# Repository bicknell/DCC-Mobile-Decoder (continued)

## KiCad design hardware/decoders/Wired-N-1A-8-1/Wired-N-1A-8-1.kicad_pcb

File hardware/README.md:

# Hardware

* [conventions](conventions/) contains documentation of hardware conventions
  used across all designs in this project.
* [reference](reference/) designs are used to understand DCC and develop
  software.  They are generally not suitable to put in a locomotive.
* [decoders](decoders/) are mobile decoders suitable for putting into 
  locomotives designed to work with the same general software as the 
  reference decoders.
* [kicad_libraries](kicad_libraries/) contains a symbol and footprint
  library that contains symbols used by the project that do not come
  with the stock KiCad distribution.

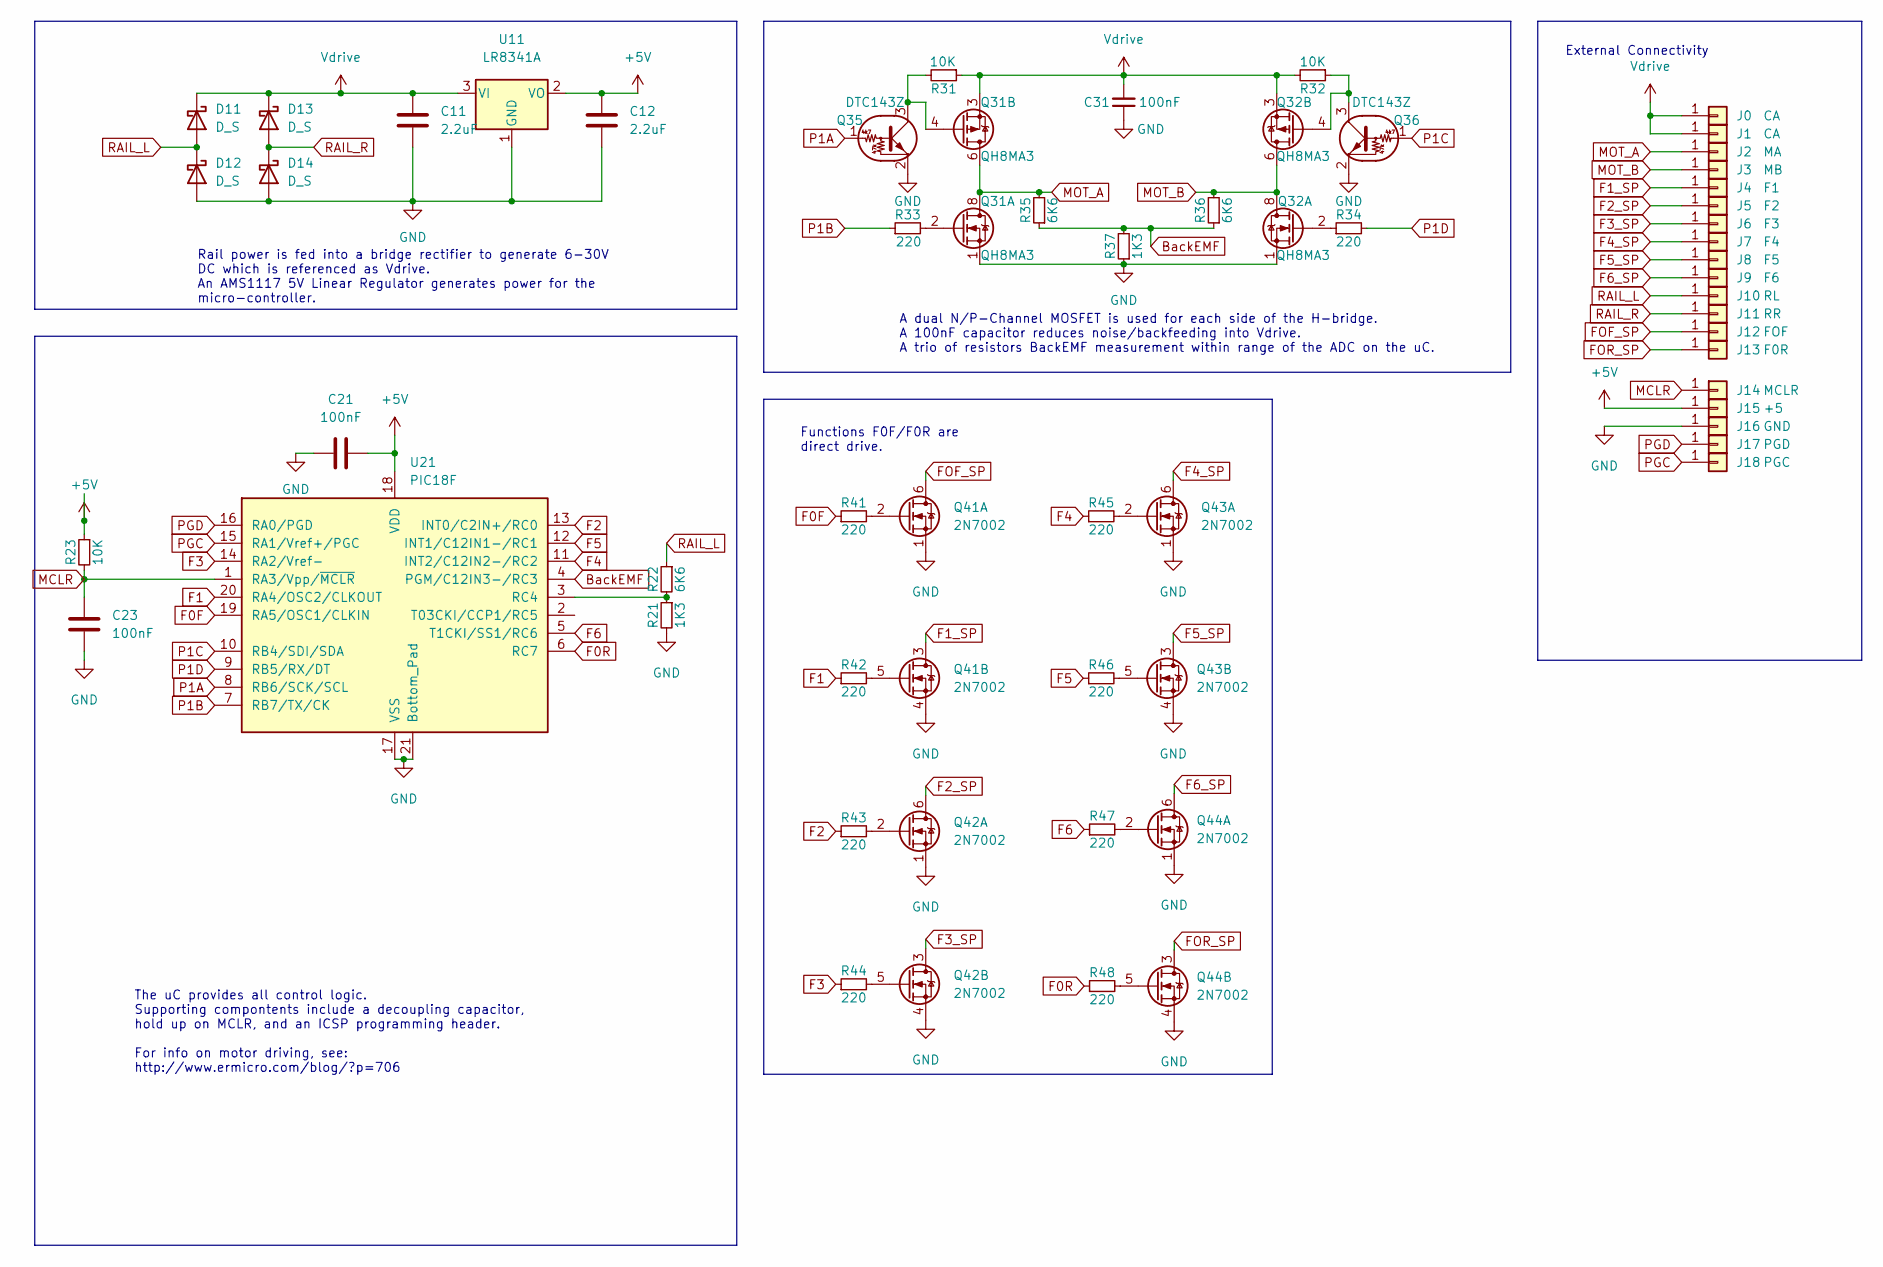
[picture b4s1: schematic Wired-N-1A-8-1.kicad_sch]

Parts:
C11, C12: 2.2uF; C_0402_1005Metric; MPN1 GRM155R6YA225KE11D
C21, C23: 100nF; C_0201_0603Metric; MPN1 GRM033R61E104KE14D
C31: 100nF; C_0402_1005Metric; MPN1 GRM155R61H104KE14D
D11, D12, D13, D14: D_S; D_SOD-523; MPN1 MSK4010
J0, J1: CA; SolderWirePad_1x01_SMD_1x2mm; MPN1 DNP
J2: MA; SolderWirePad_1x01_SMD_1x2mm; MPN1 DNP
J3: MB; SolderWirePad_1x01_SMD_1x2mm; MPN1 DNP
J4: F1; SolderWirePad_1x01_SMD_1x2mm; MPN1 DNP
J5: F2; SolderWirePad_1x01_SMD_1x2mm; MPN1 DNP
J6: F3; SolderWirePad_1x01_SMD_1x2mm; MPN1 DNP
J7: F4; SolderWirePad_1x01_SMD_1x2mm; MPN1 DNP
J8: F5; SolderWirePad_1x01_SMD_1x2mm; MPN1 DNP
J9: F6; SolderWirePad_1x01_SMD_1x2mm; MPN1 DNP
J10: RL; SolderWirePad_1x01_SMD_1x2mm; MPN1 DNP
J11: RR; SolderWirePad_1x01_SMD_1x2mm; MPN1 DNP
J12: FOF; SolderWirePad_1x01_SMD_1x2mm; MPN1 DNP
J13: F0R; SolderWirePad_1x01_SMD_1x2mm; MPN1 DNP
J14: MCLR; SolderWirePad_1x01_SMD_1x2mm; MPN1 DNP
J15: +5; SolderWirePad_1x01_SMD_1x2mm; MPN1 DNP
J16: GND; SolderWirePad_1x01_SMD_1x2mm; MPN1 DNP
J17: PGD; SolderWirePad_1x01_SMD_1x2mm; MPN1 DNP
J18: PGC; SolderWirePad_1x01_SMD_1x2mm; MPN1 DNP
Q31, Q32: QH8MA3; TSMT8; MPN1 QH8MA3 QH8MA3
Q35, Q36: DTC143Z; SOT-723; MPN1 DTC143ZM
Q41, Q42, Q43, Q44: 2N7002; SOT-363_SC-70-6; MPN1 2N7002KD
R21, R37: 1K3; R_0201_0603Metric; MPN1 0201WMF1331TEE
R22, R35, R36: 6K6; R_0201_0603Metric; MPN1 0201WMF665KTEE
R23: 10K; R_0201_0603Metric; MPN1 0201WMF1002TEE
R31, R32: 10K; R_0201_0603Metric; MPN1 0201WMF2200TEE
R33, R34, R41, R42, R43, R44, R45, R46, R47, R48: 220; R_0201_0603Metric; MPN1 0201WMF2200TEE
U11: LR8341A; SOT-23; MPN1 LR8341A-T50
U21: PIC18F; VQFN-20-1EP_3x3mm_P0.4mm_EP1.7x1.7mm; MPN1 PIC18F06Q40

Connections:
+5V: C12.1, C21.2, J15.1, R23.1, U11.2 (VO), U21.18 (VDD)
BackEMF: R35.1, R36.1, R37.2, U21.4 (PGM/C12IN3-/RC3)
F0F: R41.1, U21.19 (RA5/OSC1/CLKIN)
F0R: R48.1, U21.6 (RC7)
F1: R42.1, U21.20 (RA4/OSC2/CLKOUT)
F1_SP: J4.1, Q41.3 (D)
F2: R43.1, U21.13 (INT0/C2IN+/RC0)
F2_SP: J5.1, Q42.6 (D)
F3: R44.1, U21.14 (RA2/Vref-)
F3_SP: J6.1, Q42.3 (D)
F4: R45.1, U21.11 (INT2/C12IN2-/RC2)
F4_SP: J7.1, Q43.6 (D)
F5: R46.1, U21.12 (INT1/C12IN1-/RC1)
F5_SP: J8.1, Q43.3 (D)
F6: R47.1, U21.5 (T1CKI/SS1/RC6)
F6_SP: J9.1, Q44.6 (D)
FOF_SP: J12.1, Q41.6 (D)
FOR_SP: J13.1, Q44.3 (D)
GND: C11.2, C12.2, C21.1, C23.1, C31.1, D12.2 (A), D14.2 (A), J16.1, Q31.1 (S), Q32.1 (S), Q35.2 (E), Q36.2 (E), Q41.1 (S), Q41.4 (S), Q42.1 (S), Q42.4 (S), Q43.1 (S), Q43.4 (S), Q44.1 (S), Q44.4 (S), R21.2, R37.1, U11.1 (GND), U21.17 (VSS), U21.21 (Bottom_Pad)
MCLR: C23.2, J14.1, R23.2, U21.1 (RA3/Vpp/~MCLR)
MOT_A: J2.1, Q31.5 (D), Q31.6 (D), Q31.7 (D), Q31.8 (D), R35.2
MOT_B: J3.1, Q32.5 (D), Q32.6 (D), Q32.7 (D), Q32.8 (D), R36.2
unnamed: Q31.2 (G), R33.2
unnamed: Q32.2 (G), R34.1
unnamed: Q31.4 (G), Q35.3 (C), R31.2
unnamed: Q41.2 (G), R41.2
unnamed: Q41.5 (G), R42.2
unnamed: Q42.2 (G), R43.2
unnamed: Q42.5 (G), R44.2
unnamed: Q43.2 (G), R45.2
unnamed: Q43.5 (G), R46.2
unnamed: Q44.2 (G), R47.2
unnamed: Q44.5 (G), R48.2
unnamed: R21.1, R22.2, U21.3 (RC4)
unnamed: Q32.4 (G), Q36.3 (C), R32.1
P1A: Q35.1 (B), U21.8 (RB6/SCK/SCL)
P1B: R33.1, U21.7 (RB7/TX/CK)
P1C: Q36.1 (B), U21.10 (RB4/SDI/SDA)
P1D: R34.2, U21.9 (RB5/RX/DT)
PGC: J18.1, U21.15 (RA1/Vref+/PGC)
PGD: J17.1, U21.16 (RA0/PGD)
RAIL_L: D11.2 (A), D12.1 (K), J10.1, R22.1
RAIL_R: D13.2 (A), D14.1 (K), J11.1
Vdrive: C11.1, C31.2, D11.1 (K), D13.1 (K), J0.1, J1.1, Q31.3 (1), Q32.3 (1), R31.1, R32.2, U11.3 (VI)

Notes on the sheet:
External Connectivity
The uC provides all control logic. Supporting compontents include a decoupling capacitor, hold up on MCLR, and an ICSP programming header. For info on motor driving, see: http://www.ermicro.com/blog/?p=706
A dual N/P-Channel MOSFET is used for each side of the H-bridge. A 100nF capacitor reduces noise/backfeeding into Vdrive. A trio of resistors BackEMF measurement within range of the ADC on the uC.
Functions F0F/F0R are direct drive.
Rail power is fed into a bridge rectifier to generate 6-30V DC which is referenced as Vdrive. An AMS1117 5V Linear Regulator generates power for the micro-controller.

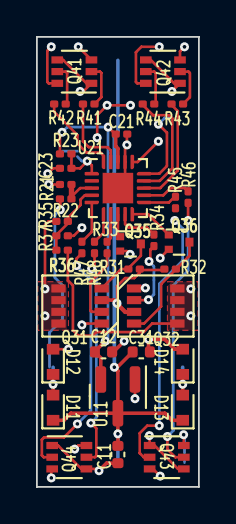
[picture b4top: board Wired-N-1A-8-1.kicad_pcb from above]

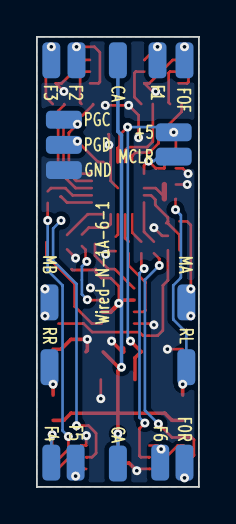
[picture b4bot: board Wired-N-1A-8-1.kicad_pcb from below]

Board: 2 copper layers, 9.0 x 25.0 mm, 56 parts (19 on the bottom side), 44 nets.

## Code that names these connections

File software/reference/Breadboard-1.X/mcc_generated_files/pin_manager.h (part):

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// get/set IO_F1 aliases
#define IO_F1_TRIS                 TRISAbits.TRISA0
#define IO_F1_LAT                  LATAbits.LATA0
#define IO_F1_PORT                 PORTAbits.RA0
#define IO_F1_WPU                  WPUAbits.WPUA0
#define IO_F1_OD                   ODCONAbits.ODCA0
#define IO_F1_ANS                  ANSELAbits.ANSELA0
#define IO_F1_SetHigh()            do { LATAbits.LATA0 = 1; } while(0)
#define IO_F1_SetLow()             do { LATAbits.LATA0 = 0; } while(0)
#define IO_F1_Toggle()             do { LATAbits.LATA0 = ~LATAbits.LATA0; } while(0)
#define IO_F1_GetValue()           PORTAbits.RA0
#define IO_F1_SetDigitalInput()    do { TRISAbits.TRISA0 = 1; } while(0)
#define IO_F1_SetDigitalOutput()   do { TRISAbits.TRISA0 = 0; } while(0)
#define IO_F1_SetPullup()          do { WPUAbits.WPUA0 = 1; } while(0)
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// get/set IO_F2 aliases
#define IO_F2_TRIS                 TRISAbits.TRISA1
#define IO_F2_LAT                  LATAbits.LATA1
#define IO_F2_PORT                 PORTAbits.RA1
#define IO_F2_WPU                  WPUAbits.WPUA1
#define IO_F2_OD                   ODCONAbits.ODCA1
#define IO_F2_ANS                  ANSELAbits.ANSELA1
#define IO_F2_SetHigh()            do { LATAbits.LATA1 = 1; } while(0)
#define IO_F2_SetLow()             do { LATAbits.LATA1 = 0; } while(0)
#define IO_F2_Toggle()             do { LATAbits.LATA1 = ~LATAbits.LATA1; } while(0)
#define IO_F2_GetValue()           PORTAbits.RA1
#define IO_F2_SetDigitalInput()    do { TRISAbits.TRISA1 = 1; } while(0)
#define IO_F2_SetDigitalOutput()   do { TRISAbits.TRISA1 = 0; } while(0)
#define IO_F2_SetPullup()          do { WPUAbits.WPUA1 = 1; } while(0)
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// get/set IO_F3 aliases
#define IO_F3_TRIS                 TRISAbits.TRISA2
#define IO_F3_LAT                  LATAbits.LATA2
#define IO_F3_PORT                 PORTAbits.RA2
#define IO_F3_WPU                  WPUAbits.WPUA2
#define IO_F3_OD                   ODCONAbits.ODCA2
#define IO_F3_ANS                  ANSELAbits.ANSELA2
#define IO_F3_SetHigh()            do { LATAbits.LATA2 = 1; } while(0)
#define IO_F3_SetLow()             do { LATAbits.LATA2 = 0; } while(0)
#define IO_F3_Toggle()             do { LATAbits.LATA2 = ~LATAbits.LATA2; } while(0)
#define IO_F3_GetValue()           PORTAbits.RA2
#define IO_F3_SetDigitalInput()    do { TRISAbits.TRISA2 = 1; } while(0)
#define IO_F3_SetDigitalOutput()   do { TRISAbits.TRISA2 = 0; } while(0)
#define IO_F3_SetPullup()          do { WPUAbits.WPUA2 = 1; } while(0)
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// get/set IO_DCC aliases
#define IO_DCC_TRIS                 TRISAbits.TRISA4
#define IO_DCC_LAT                  LATAbits.LATA4
#define IO_DCC_PORT                 PORTAbits.RA4
#define IO_DCC_WPU                  WPUAbits.WPUA4
#define IO_DCC_OD                   ODCONAbits.ODCA4
#define IO_DCC_ANS                  ANSELAbits.ANSELA4
#define IO_DCC_SetHigh()            do { LATAbits.LATA4 = 1; } while(0)
#define IO_DCC_SetLow()             do { LATAbits.LATA4 = 0; } while(0)
#define IO_DCC_Toggle()             do { LATAbits.LATA4 = ~LATAbits.LATA4; } while(0)
#define IO_DCC_GetValue()           PORTAbits.RA4
#define IO_DCC_SetDigitalInput()    do { TRISAbits.TRISA4 = 1; } while(0)
#define IO_DCC_SetDigitalOutput()   do { TRISAbits.TRISA4 = 0; } while(0)
#define IO_DCC_SetPullup()          do { WPUAbits.WPUA4 = 1; } while(0)
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// get/set IO_BACKEMF aliases
#define IO_BACKEMF_TRIS                 TRISAbits.TRISA5
#define IO_BACKEMF_LAT                  LATAbits.LATA5
#define IO_BACKEMF_PORT                 PORTAbits.RA5
#define IO_BACKEMF_WPU                  WPUAbits.WPUA5
#define IO_BACKEMF_OD                   ODCONAbits.ODCA5
#define IO_BACKEMF_ANS                  ANSELAbits.ANSELA5
#define IO_BACKEMF_SetHigh()            do { LATAbits.LATA5 = 1; } while(0)
#define IO_BACKEMF_SetLow()             do { LATAbits.LATA5 = 0; } while(0)
#define IO_BACKEMF_Toggle()             do { LATAbits.LATA5 = ~LATAbits.LATA5; } while(0)
#define IO_BACKEMF_GetValue()           PORTAbits.RA5
#define IO_BACKEMF_SetDigitalInput()    do { TRISAbits.TRISA5 = 1; } while(0)
#define IO_BACKEMF_SetDigitalOutput()   do { TRISAbits.TRISA5 = 0; } while(0)
#define IO_BACKEMF_SetPullup()          do { WPUAbits.WPUA5 = 1; } while(0)
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// get/set IO_F0R aliases
#define IO_F0R_TRIS                 TRISBbits.TRISB4
#define IO_F0R_LAT                  LATBbits.LATB4
#define IO_F0R_PORT                 PORTBbits.RB4
#define IO_F0R_WPU                  WPUBbits.WPUB4
#define IO_F0R_OD                   ODCONBbits.ODCB4
#define IO_F0R_ANS                  ANSELBbits.ANSELB4
#define IO_F0R_SetHigh()            do { LATBbits.LATB4 = 1; } while(0)
#define IO_F0R_SetLow()             do { LATBbits.LATB4 = 0; } while(0)
#define IO_F0R_Toggle()             do { LATBbits.LATB4 = ~LATBbits.LATB4; } while(0)
#define IO_F0R_GetValue()           PORTBbits.RB4
#define IO_F0R_SetDigitalInput()    do { TRISBbits.TRISB4 = 1; } while(0)
#define IO_F0R_SetDigitalOutput()   do { TRISBbits.TRISB4 = 0; } while(0)
#define IO_F0R_SetPullup()          do { WPUBbits.WPUB4 = 1; } while(0)
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#define RB5_SetHigh()            do { LATBbits.LATB5 = 1; } while(0)
#define RB5_SetLow()             do { LATBbits.LATB5 = 0; } while(0)
#define RB5_Toggle()             do { LATBbits.LATB5 = ~LATBbits.LATB5; } while(0)
#define RB5_GetValue()              PORTBbits.RB5
#define RB5_SetDigitalInput()    do { TRISBbits.TRISB5 = 1; } while(0)
#define RB5_SetDigitalOutput()   do { TRISBbits.TRISB5 = 0; } while(0)
#define RB5_SetPullup()             do { WPUBbits.WPUB5 = 1; } while(0)
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// get/set IO_F0F aliases
#define IO_F0F_TRIS                 TRISBbits.TRISB6
#define IO_F0F_LAT                  LATBbits.LATB6
#define IO_F0F_PORT                 PORTBbits.RB6
#define IO_F0F_WPU                  WPUBbits.WPUB6
#define IO_F0F_OD                   ODCONBbits.ODCB6
#define IO_F0F_ANS                  ANSELBbits.ANSELB6
#define IO_F0F_SetHigh()            do { LATBbits.LATB6 = 1; } while(0)
#define IO_F0F_SetLow()             do { LATBbits.LATB6 = 0; } while(0)
#define IO_F0F_Toggle()             do { LATBbits.LATB6 = ~LATBbits.LATB6; } while(0)
#define IO_F0F_GetValue()           PORTBbits.RB6
#define IO_F0F_SetDigitalInput()    do { TRISBbits.TRISB6 = 1; } while(0)
#define IO_F0F_SetDigitalOutput()   do { TRISBbits.TRISB6 = 0; } while(0)
#define IO_F0F_SetPullup()          do { WPUBbits.WPUB6 = 1; } while(0)
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#define RB7_SetHigh()            do { LATBbits.LATB7 = 1; } while(0)
#define RB7_SetLow()             do { LATBbits.LATB7 = 0; } while(0)
#define RB7_Toggle()             do { LATBbits.LATB7 = ~LATBbits.LATB7; } while(0)
#define RB7_GetValue()              PORTBbits.RB7
#define RB7_SetDigitalInput()    do { TRISBbits.TRISB7 = 1; } while(0)
#define RB7_SetDigitalOutput()   do { TRISBbits.TRISB7 = 0; } while(0)
#define RB7_SetPullup()             do { WPUBbits.WPUB7 = 1; } while(0)
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// get/set IO_F4 aliases
#define IO_F4_TRIS                 TRISCbits.TRISC0
#define IO_F4_LAT                  LATCbits.LATC0
#define IO_F4_PORT                 PORTCbits.RC0
#define IO_F4_WPU                  WPUCbits.WPUC0
#define IO_F4_OD                   ODCONCbits.ODCC0
#define IO_F4_ANS                  ANSELCbits.ANSELC0
#define IO_F4_SetHigh()            do { LATCbits.LATC0 = 1; } while(0)
#define IO_F4_SetLow()             do { LATCbits.LATC0 = 0; } while(0)
#define IO_F4_Toggle()             do { LATCbits.LATC0 = ~LATCbits.LATC0; } while(0)
#define IO_F4_GetValue()           PORTCbits.RC0
#define IO_F4_SetDigitalInput()    do { TRISCbits.TRISC0 = 1; } while(0)
#define IO_F4_SetDigitalOutput()   do { TRISCbits.TRISC0 = 0; } while(0)
#define IO_F4_SetPullup()          do { WPUCbits.WPUC0 = 1; } while(0)
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// get/set IO_F5 aliases
#define IO_F5_TRIS                 TRISCbits.TRISC1
#define IO_F5_LAT                  LATCbits.LATC1
#define IO_F5_PORT                 PORTCbits.RC1
#define IO_F5_WPU                  WPUCbits.WPUC1
#define IO_F5_OD                   ODCONCbits.ODCC1
#define IO_F5_ANS                  ANSELCbits.ANSELC1
#define IO_F5_SetHigh()            do { LATCbits.LATC1 = 1; } while(0)
#define IO_F5_SetLow()             do { LATCbits.LATC1 = 0; } while(0)
#define IO_F5_Toggle()             do { LATCbits.LATC1 = ~LATCbits.LATC1; } while(0)
#define IO_F5_GetValue()           PORTCbits.RC1
#define IO_F5_SetDigitalInput()    do { TRISCbits.TRISC1 = 1; } while(0)
#define IO_F5_SetDigitalOutput()   do { TRISCbits.TRISC1 = 0; } while(0)
#define IO_F5_SetPullup()          do { WPUCbits.WPUC1 = 1; } while(0)
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// get/set IO_F6 aliases
#define IO_F6_TRIS                 TRISCbits.TRISC2
#define IO_F6_LAT                  LATCbits.LATC2
#define IO_F6_PORT                 PORTCbits.RC2
#define IO_F6_WPU                  WPUCbits.WPUC2
#define IO_F6_OD                   ODCONCbits.ODCC2
#define IO_F6_ANS                  ANSELCbits.ANSELC2
#define IO_F6_SetHigh()            do { LATCbits.LATC2 = 1; } while(0)
#define IO_F6_SetLow()             do { LATCbits.LATC2 = 0; } while(0)
#define IO_F6_Toggle()             do { LATCbits.LATC2 = ~LATCbits.LATC2; } while(0)
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
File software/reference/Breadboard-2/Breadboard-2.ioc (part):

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Mcu.Name=STM32F103R(8-B)Tx
Mcu.Package=LQFP64
Mcu.UserName=STM32F103RBTx
PA12.GPIOParameters=GPIO_PuPd,GPIO_Label
PA12.GPIO_Label=DCC_IN
PA12.GPIO_PuPd=GPIO_PULLUP
PA12.Signal=S_TIM1_ETR
PA13.Mode=Serial_Wire
PA13.Signal=SYS_JTMS-SWDIO
PA14.Mode=Serial_Wire
PA14.Signal=SYS_JTCK-SWCLK
PA2.Mode=Asynchronous
PA2.Signal=USART2_TX
PA3.Mode=Asynchronous
PA3.Signal=USART2_RX
PA5.GPIOParameters=GPIO_Speed,PinState,GPIO_Label
PA5.GPIO_Label=STATUS_LED
PA5.GPIO_Speed=GPIO_SPEED_FREQ_LOW
PA5.PinState=GPIO_PIN_RESET
PA5.Signal=GPIO_Output
RCC.SYSCLKFreq_VALUE=64000000
RCC.SYSCLKSource=RCC_SYSCLKSOURCE_PLLCLK
board=custom

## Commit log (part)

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2022-11-08 Adding LICENSE and basic directory structure.
2022-11-08 First draft of hardware constraints.
2022-11-08 More constraints for the initial list.
2022-11-11 Ignore KiCAD temporary files.
2022-11-11 Initial reference design PCB commit.
2022-11-11 Cleaned up the PCB routing.
2022-11-11 Initial description of the schematic and PCB.
2022-11-12 More basic info added.
2022-11-12 Added CALCULATIONS information.
2022-11-12 Change from +12v to Vdrive.
2022-11-12 Added Contributing section.
2022-11-13 Update data sheet values and calculations. Add missing components.
2022-11-13 Added data sheets. Moved schematic values for readability.
2022-11-13 Lots of cleanup, finalizing the specifications for Breadboard-1.
2022-11-13 Added resistor and capacitor data.
2022-11-13 Added MOSFET specifications.
2022-11-13 Minor corrections to the overview document. Refill PCB.
2022-11-24 Add a 3D render of the board.
2022-11-24 Crop better.
2022-11-24 Shrink size.
2022-11-24 Added V3V3USB capacitor and USB Micro-B port for debugging.
2022-11-24 Move USB to the External Connectivity section.
2022-11-24 Update notes to be more clear about circuit design.
2022-11-24 Regenerate image to match current schematic.
2022-11-24 Make functions symmetrical.
2022-12-01 Made Wired-N-1A-6-1 prettier, and easier to follow.
2022-12-01 Moved to SOD-123 diodes for cheaper, better rating parts.
2022-12-01 Add a blank project for the DCC library, created in MPLabX
2022-12-08 Chip selection update, new symbols, improved reference design.
    Updated the chip selection document based on availability.
    Added new symbols for the chips in the chip selection document.
    Switched the reference design to an SSOP-20 package and improved the
    layout in general.
2022-12-08 Initial draft of feature documentation.
2022-12-08 Update to github Markdown syntax.
2022-12-08 Making the documentation more clear and organized.
2022-12-08 Make links match directory names.
2022-12-08 Correct nesting of lists.
2022-12-08 Organize the index a bit better.
2022-12-08 Update to PIC18F06Q40 specifications.
2022-12-08 Minor doc updates to go with the updated CPU.
2022-12-08 Updated to the new processor and lots of board layout cleanup.
2022-12-12 Updating the current project status.
2022-12-12 Position cleanup, better trace routing.
2022-12-12 Fixed typo, updated about future.
2022-12-12 Image to match the latest board.
2022-12-12 Add a listing of other projects.
2022-12-12 Added 3D render.
2022-12-12 Fix image syntax.
2022-12-12 Updated commercial license description.
2022-12-12 Initial documentation of IDE config.
2022-12-13 Add a PDF version of the schematic.
2022-12-13 Fixed broadcast decoder reset packet handling.
    Ran "make clean" before comitting, which is removing all of the build
    artifacts.
    Regenerated MCC files.
2022-12-13 Implement suggestions from DCC-EX friends.
    Set TMR2 period to 80us.
    Implemented consist address feature.
    Move variables out of dcc_decode and into globals for performance.
    Moved checksum inside dcc_decode to make interface cleaner.
    Reordered logic to check the speed/direction packets first, and the
    function group packets second to improve performance.
2022-12-13 All debugs should be turned off in the master repo.
2022-12-13 Clean up CV29/NDOT handling.
2022-12-13 Properly implement C19 consisting, including function mapping by CV21/CV22.
    Clean up some bad printf's with extra arguments.
    Improve NDOT (and consisted NDOT) handling in motor_control.
2022-12-14 Populate software index.
2022-12-14 Initial documentation of the features and functionality supported by the code.
2022-12-14 Implement read-only CV's.
2022-12-14 Correct typo, flag read only CV's.
2022-12-16 Clarified the current state of the project.
2022-12-17 Initial version of a fully manual breadboard version of the circuit.
2022-12-17 Add a few more details.
2022-12-17 Initial version of Manual-1.
2022-12-17 Minor tweak to BOM.
2022-12-17 Added a picture with some explanation.
2022-12-19 Initial support for S-9.2.3 service mode programming.
    Address mode.
    Direct mode.
    Register mode.
    Paged mode.
    Does not yet support either appendix.
2022-12-19 Update status on service mode.
2022-12-19 Updated feature list with Service Mode information.
2022-12-20 Reset handling improvement, fixed bit logic, cleaned Page/Register code.
2022-12-22 Add pre-biased transistors to drive high side. Update LED part to more common.
2022-12-22 Updated schematic PDF based on last edits.
2022-12-22 Updated TMR0 to 20ms, implemented dropping from Service Mode.
    Renamed dcc_performance to dcc_periodic to better reflect it's function.
    Set TMR0 to call it every 20ms.
    Update statitics printing to continue to be once per second.
    Implement dropping out of a service mode.
    Move the CV8=8 factory reset logic into the CV handling so that
    it works no matter how the CV is written.
2022-12-23 Bring inline with SOT-23 rework.
2022-12-27 Extended the refactor to include a DRV8870DDA motor driver.
    Generates parts reduction, at a slightly increased cost.
2023-02-19 Initial take at function effects.
    Changes TMR0 periodic to 25ms to create 40 bits/sec of output.
    Adds CV's 120-126 for function effect selection.
    Adds function_control() in hardware.c to manipulate the output.
    Adds effects[][] array in hardware.c with the bitpatterns for the output.
    Note that several of these are incomplete at this time.
2023-09-08 Added pin-header for oscilloscope.
    Provide connection points to monitor the DCC signal, motor driver
    inputs and backEMF.
    Additional prettying up of the traces.
2023-09-08 Bring documentation inline with previous technical updates.
2023-09-10 Cleanup of the final PCB.
    Moved components to grid coordinates.
    Added in some labels for the user.
    Cleaned up some trace routing, and made it pretty where possible.
2023-09-10 Generated updated .JPG and .PDF for documentation.
2023-09-11 Minor design tweak, update documentation.
    Moved the MCLEAR hold up components to make the board design cleaner.
    Updated all the documentation to match the current configuration.
2023-09-11 Add warning about resistor to README.
2023-09-11 Bring inline with Breadboard-1 reference design.
    Add digital transitor drivers for the high side of the H-Bridge.
    Add third BEMF resistor.
    Relocate noise capacitor.
2023-09-14 Manufacturability changes.
    Added 3 fiducial markers to support pick and place in volume.
    Resized all the traces to be manufacturable with the popular board fabs.
    Moved traces based on the new size.
    Standardized vias to one size larger than the general manufacturing minimum.
    Improved grounding around the CPU.
2023-09-15 Updated BOM to optimize for JLCPCB production.
    Used as many JLCPCB "basic" parts as possible, optimized for
    the cheapest parts in stock as of today.
2023-09-15 Updates based on feedback from JLCPCB online tools.
2023-09-16 Ignore more OSX cache files.
2023-09-16 Pile of minor corrections for sharing and production.
    1. Remove .DS_Store files mistakenly added.
    2. Correctly relatively path project footprints and symbols.
    3. Add footprint for JLCPCB's required tooling hole to use their assembly service.
    4. Tweak a few tracks and description placements to enhance readability.
2023-09-16 Add service mode programming note.
2023-09-16 Turned feature list into checkboxes to track progress.
2023-09-16 Minor cleanup.
2023-09-16 Remove unused directory.
2023-09-18 Moved CALCULATIONS to a spreadsheet.
    Moved the calculations into a spreadsheet so that the values would
    dynamically change when components needed to be updated. Used the
    dynamic capabilities along with the JLCPCB parts list to update
    resistor values to have more common values and use JLCPCB basic
    parts values.
    Determined also that the calculations on the DCC input were wrong
2023-09-18 Added missing ground trace and regenerated image.
2023-09-18 Save JLCPCB preferred gerber options.
2023-09-18 Missed 'Load En' in previous rework.
2023-09-18 Update board color to blue w/white silkscreen.
2023-09-19 Initial draft of a super-mineature F0F/F0R N-scale decoder.
2023-09-20 Added pngs as required by subreddit rules.
2023-09-20 Updated png files to make things more clear.
2023-09-20 Update CHIP-SELECTION.md
    Correct error in N/Z chip form factor. REB part numbers are VFQN-20 parts.
2023-09-24 Renamed Wired-N-1A-6-1 to Wired-N-1A-8-1.
2023-09-25 Improved calculations, and other updates as a result.
    Switched to tantalum capacitors per the data sheet recommendation
    for the regulator. Reworked board to accomodate.
    Switched DCC input to be through a MOSFET to accomodate the track
    voltage range.
    Re-organized schematic so the blocks make more sense, changed to
    US Letter paper, and re-annotated so each block has it's own 10's
2023-09-25 Fixed broken links and generated image and schematics.
2023-09-26 Switched regulator, added "super capacitor" location.
    Switched the linear regulator to a SE8633X2-HF which has superior
    performance characteristics. Switched back to 0805 10uF resistors
    as a result. Reworked regulator area, using copper fills to lower
    resistance between components per data sheet recomendation.
    Added C11, a spot for an electrolytic "super capacitor" of up to 1000uF
    to help smooth out input electrical issues. Moved a few traces to make
2023-09-26 Crop picture to the right size.
2023-09-26 Updated description to include super capacitor.
2023-09-27 Minor corrections to specs.
2023-09-27 Crop image.
2023-09-29 Plot paramters to get good gerbers.
2023-10-02 Correct over-voltage on high side drive.
    The P-Channel MOSFET gate would be driven to 0v by the old driver
    circuit. When the DCC voltage is > 20v, this exceeds the Vgs
    maximum of the part.
    Added another resistor to make a voltage divider cutting the voltage
    in half, and thus driving the gate at 15v when Vdrive is 30v. Now
    Vgs is always within range of the part.
2023-10-02 Initial draft of the decoder.
2023-10-04 Clarified function numbering.
2023-10-04 Ensure power traces can handle 1A, cosmetic cleanup.
    1) Enlarged traces that will carry large currents to insure they
    are of sufficient size.
    2) Make sure everything was aligned on an inch/mil grid. Moved components
    to provide more board space for the wider traces. General make it pretty.
2023-10-04 Fixed up text on the fab layer.
2023-10-04 Small corrections.
2023-10-04 Update to be current.
2023-10-06 Software with working function effects & motor control.
    Implemented basic function effects, some look good, some still
    need tweaking.
    Corrected the motor control code so the outputs are correct.
2023-10-06 Correct lighting features.
2023-10-06 Had NDOT listed twice.
2023-10-06 Cosmetic cleanup, removed unnecessary global scoped variables.
2023-10-07 Updated MOSFETS to be ESD protected versions. Updated calculations.
2023-10-08 Parts update, moved descriptive language from README to CALCULATIONS.
    Updated MOSFET selection, again.
    Moved all block descriptions from README into CALCULATIONS so they are
    not duplicated.
    Improved some descriptions.
2023-10-18 Improve manufacturability.
2023-10-18 Updated image to match manufacturability improvements.
2023-10-22 Initial hardware implementation of a STM32 processor.
    Replace the SSOP-20 PIC18F processor with a TSSOP-20 STM32 processor.
    Where possible IO was kept on the same pin number to avoid re-routing
    additonal traces. Minor changes were needed to the decoupling capacitors
    as well as the programming header.
2023-10-22 Correct data sheet link.
2023-10-22 Replace +5V to +3V3 in schematic to properly reflect voltage.
2023-10-22 Move DCC_IN and BackEMF to pins with appropriate capabilities.
    STM32 does not allow software remapping of the periperhal input
    pins. The location in the PIC design (Breadboard-1) routes them
    to pins on an STM32 that are designed for the oscellator, but can
    be re-used. As such they have no ADC or Timer triggers attached
    to them.
    DCC_IN was moved to port 20, which can be routed to any of
2024-03-18 Initial partial port of software to the STM32 platform.
    This code is destined to go with Breadboard-2, but for now is being
    developed and tested on an NUCLEO-F103RB board. It's done in
    STM32CubeIDE and uses the full set of hardware abstrations.
    The motor code and function code has not yet been ported, and a
    sync between this and the PIC code needs to happen.
